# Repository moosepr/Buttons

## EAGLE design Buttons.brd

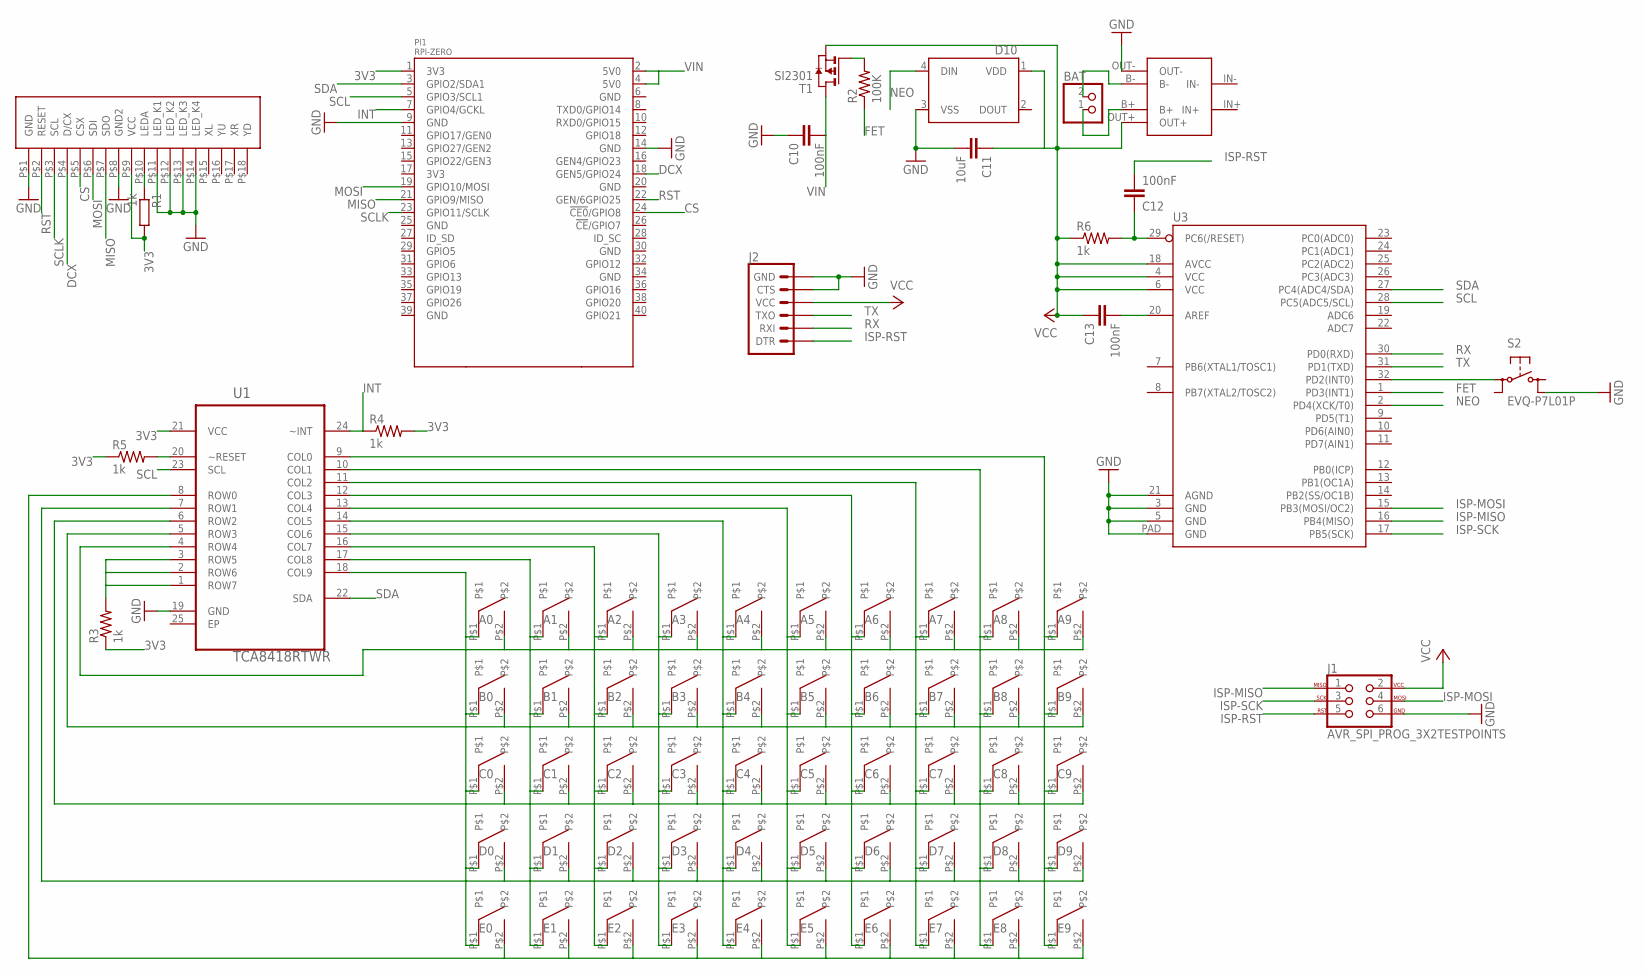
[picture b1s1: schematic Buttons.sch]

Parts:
A0, A1, A2, A3, A4, A5, A6, A7, A8, A9: 5MMSNAP
B0, B1, B2, B3, B4, B5, B6, B7, B8, B9: 5MMSNAP
BAT: JST_2PIN-SMT-RA; JST-PH-2-SMT-RA
C0, C1, C2, C3, C4, C5, C6, C7, C8, C9: 5MMSNAP
C10, C12, C13: 100nF; C0603K
C11: 10uF; C0603K
D0, D1, D2, D3, D4, D5, D6, D7, D8, D9: 5MMSNAP
D10: WS2812B
E0, E1, E2, E3, E4, E5, E6, E7, E8, E9: 5MMSNAP
J1: AVR_SPI_PROG_3X2TESTPOINTS; 2X3_TEST_POINTS
J2: 6_PIN_SERIAL_TARGETSILK; 6_PIN_SERIAL_TARGET_SIDE_W_SILK
PI1: RPI-ZERO; RASPBERRYPI_BASTELSTUBE_V13_RASPI_BOARD_B+_FULL
R1: 1k; R0805
R2: 100K; 0603-RES
R3, R4, R5, R6: 1k; 0805
S2: EVQ-P7L01P
T1: SI2301; SOT-23
U1: TCA8418RTWR; QFN50P400X400X80-25N
U3: ATMEGA328P_MLFMLF32; MLF32-PAD
U$1: 03962A
U$2: ILI9341-2.8

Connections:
3V3: PI1.1 (3V3), R1.2, R3.1, R4.2, R5.1, U1.21 (VCC), U$2.P$9 (VCC)
CS: PI1.24 (!CE0!/GPIO8), U$2.P$5 (CSX)
DCX: PI1.18 (GEN5/GPIO24), U$2.P$4 (D/CX)
FET: R2.1, U3.1 (PD3(INT1))
GND: C10.1, C11.2, D10.3 (VSS), J1.6, J2.P$5 (CTS), J2.P$6 (GND), PI1.9 (GND), PI1.14 (GND), S2.B1 (S1), U1.19 (GND), U3.3 (GND), U3.5 (GND), U3.21 (AGND), U3.PAD (GND), U$1.OUT-, U$2.P$1 (GND), U$2.P$8 (GND2), U$2.P$11 (LED_K1), U$2.P$12 (LED_K2), U$2.P$13 (LED_K3), U$2.P$14 (LED_K4)
INT: PI1.7 (GPIO4/GCKL), R4.1, U1.24 (~INT)
ISP-MISO: J1.1, U3.16 (PB4(MISO))
ISP-MOSI: J1.4, U3.15 (PB3(MOSI/OC2))
ISP-RST: C12.2, J1.5, J2.P$1 (DTR)
ISP-SCK: J1.3, U3.17 (PB5(SCK))
MISO: PI1.21 (GPIO9/MISO), U$2.P$7 (SDO)
MOSI: PI1.19 (GPIO10/MOSI), U$2.P$6 (SDI)
unnamed: S2.A, U3.32 (PD2(INT0))
unnamed: C13.2, U3.20 (AREF)
unnamed: C12.1, R6.2, U3.29 (PC6(/RESET))
unnamed: R1.1, U$2.P$10 (LEDA)
unnamed: R3.2, U1.1 (ROW7), U1.2 (ROW6), U1.3 (ROW5)
unnamed: R2.2, T1.3 (G)
unnamed: R5.2, U1.20 (~RESET)
unnamed: A9.P$1, B9.P$1, C9.P$1, D9.P$1, E9.P$1, U1.9 (COL0)
unnamed: A0.P$2, A1.P$2, A2.P$2, A3.P$2, A4.P$2, A5.P$2, A6.P$2, A7.P$2, A8.P$2, A9.P$2, U1.4 (ROW4)
unnamed: B0.P$2, B1.P$2, B2.P$2, B3.P$2, B4.P$2, B5.P$2, B6.P$2, B7.P$2, B8.P$2, B9.P$2, U1.5 (ROW3)
unnamed: C0.P$2, C1.P$2, C2.P$2, C3.P$2, C4.P$2, C5.P$2, C6.P$2, C7.P$2, C8.P$2, C9.P$2, U1.6 (ROW2)
unnamed: D0.P$2, D1.P$2, D2.P$2, D3.P$2, D4.P$2, D5.P$2, D6.P$2, D7.P$2, D8.P$2, D9.P$2, U1.7 (ROW1)
unnamed: E0.P$2, E1.P$2, E2.P$2, E3.P$2, E4.P$2, E5.P$2, E6.P$2, E7.P$2, E8.P$2, E9.P$2, U1.8 (ROW0)
unnamed: BAT.1 (2), U$1.B+
unnamed: BAT.2 (1), U$1.B-
unnamed: A0.P$1, B0.P$1, C0.P$1, D0.P$1, E0.P$1, U1.18 (COL9)
unnamed: A1.P$1, B1.P$1, C1.P$1, D1.P$1, E1.P$1, U1.17 (COL8)
unnamed: A2.P$1, B2.P$1, C2.P$1, D2.P$1, E2.P$1, U1.16 (COL7)
unnamed: A3.P$1, B3.P$1, C3.P$1, D3.P$1, E3.P$1, U1.15 (COL6)
unnamed: A4.P$1, B4.P$1, C4.P$1, D4.P$1, E4.P$1, U1.14 (COL5)
unnamed: A5.P$1, B5.P$1, C5.P$1, D5.P$1, E5.P$1, U1.13 (COL4)
unnamed: A6.P$1, B6.P$1, C6.P$1, D6.P$1, E6.P$1, U1.12 (COL3)
unnamed: A7.P$1, B7.P$1, C7.P$1, D7.P$1, E7.P$1, U1.11 (COL2)
unnamed: A8.P$1, B8.P$1, C8.P$1, D8.P$1, E8.P$1, U1.10 (COL1)
NEO: D10.4 (DIN), U3.2 (PD4(XCK/T0))
RST: PI1.22 (GEN/6GPIO25), U$2.P$2 (RESET)
RX: J2.P$3 (RXI), U3.30 (PD0(RXD))
SCL: PI1.5 (GPIO3/SCL1), U1.23 (SCL), U3.28 (PC5(ADC5/SCL))
SCLK: PI1.23 (GPIO11/SCLK), U$2.P$3 (SCL)
SDA: PI1.3 (GPIO2/SDA1), U1.22 (SDA), U3.27 (PC4(ADC4/SDA))
TX: J2.P$2 (TXO), U3.31 (PD1(TXD))
VCC: C11.1, C13.1, D10.1 (VDD), J1.2, J2.P$4 (VCC), R6.1, T1.2 (S), U3.4 (VCC), U3.6 (VCC), U3.18 (AVCC), U$1.OUT+
VIN: C10.2, PI1.2 (5V0), PI1.4 (5V0), T1.1 (D)

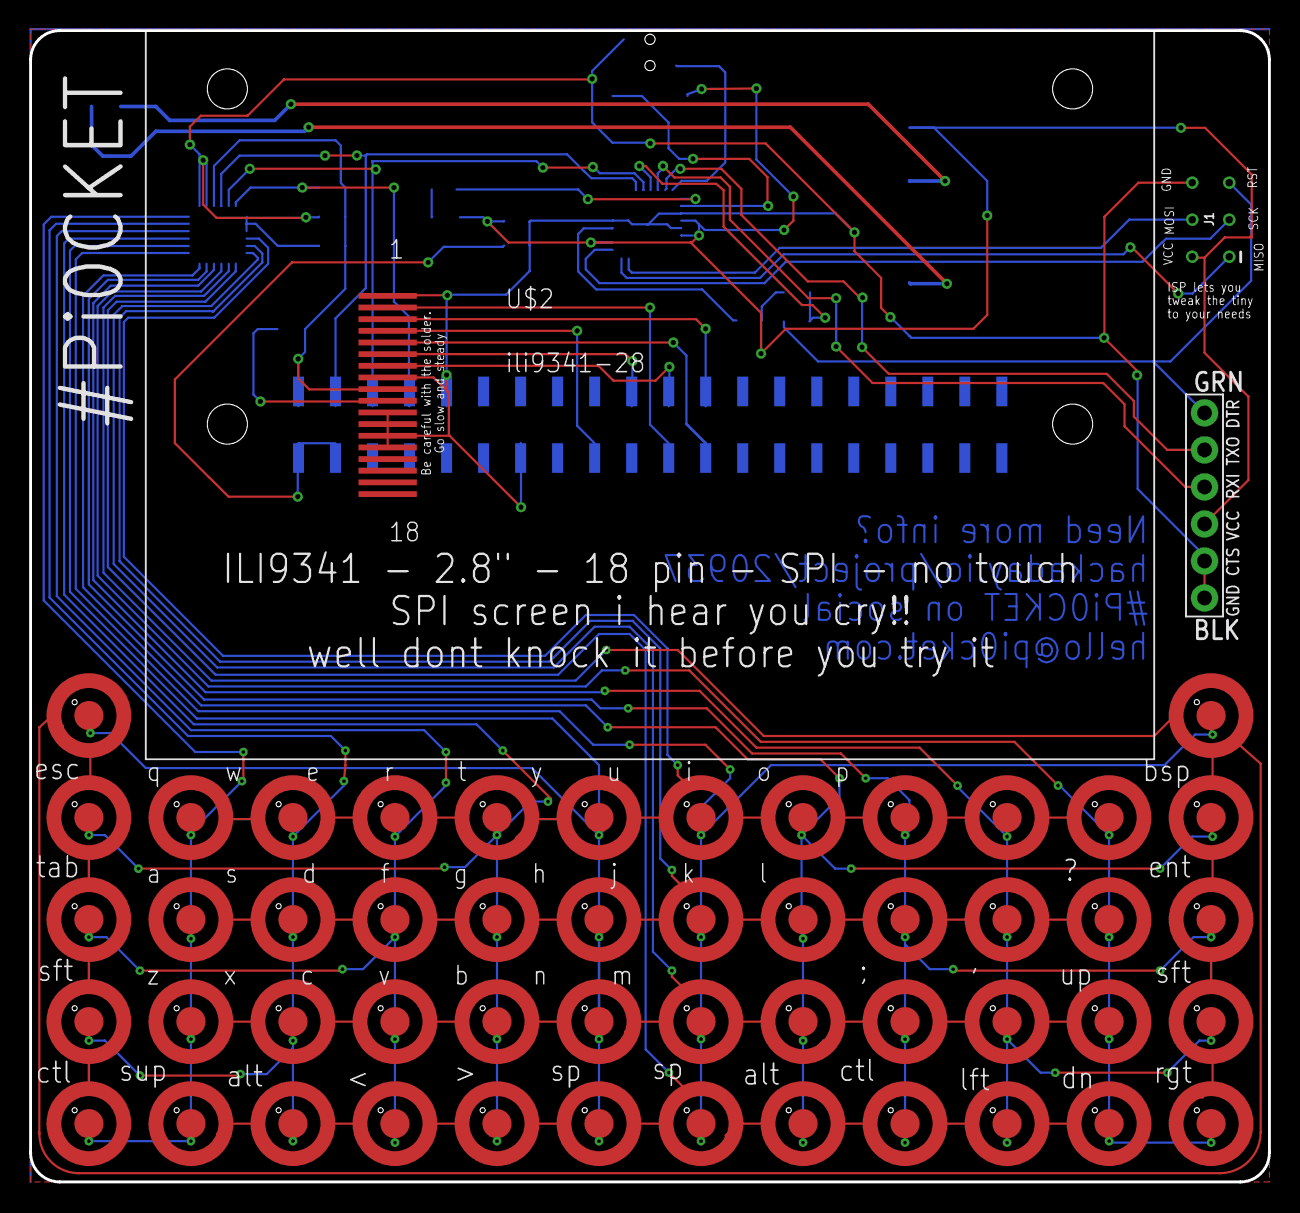
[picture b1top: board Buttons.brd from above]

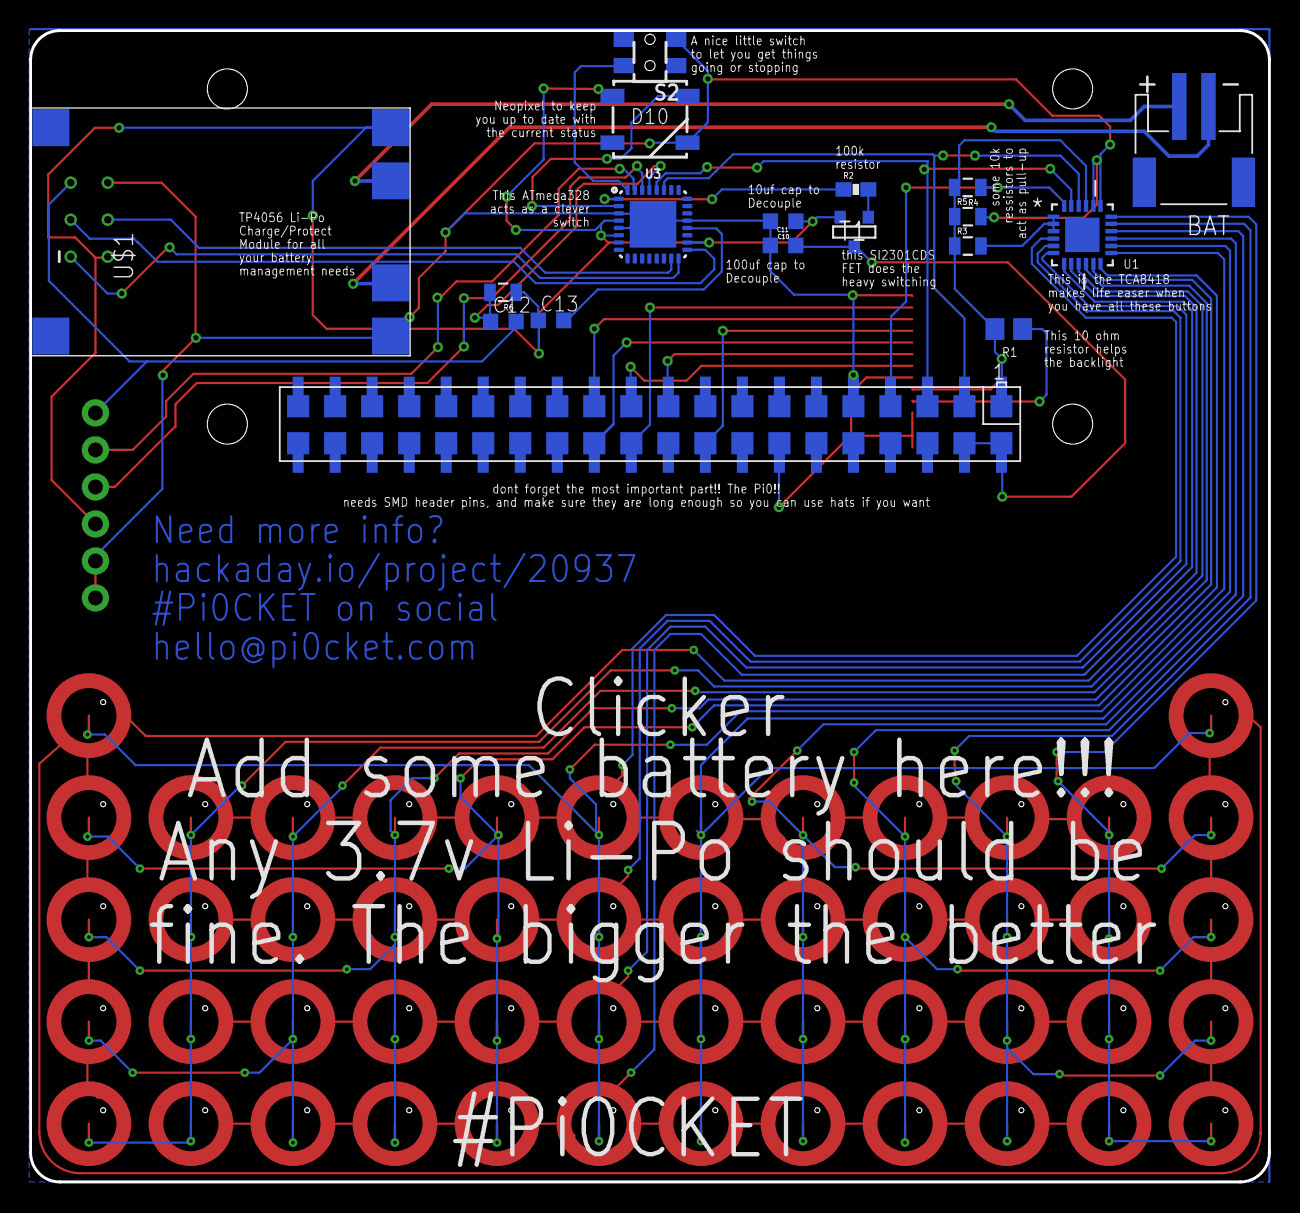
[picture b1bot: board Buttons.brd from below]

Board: 2 copper layers, 85.0 x 79.0 mm, 71 parts (18 on the bottom side), 45 nets.

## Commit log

2017-04-16 in the begining, peter created the pcb, and it was without form and void
2017-08-17 getting there!!
2017-08-22 this could be the one neo!
2017-08-23 nailed it!
2017-08-25 final?
2017-11-05 changed the tiny85 to a tiny88, the power button is now a side press jobby, and moved to the back along with the neopixel.
2017-11-05 some polish
2018-01-16 changed to atmega328
2018-02-27 fixed issue with power button footprint

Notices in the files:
parts and their libraries:
SparkFun-Passives: Licensing: CC v3.0 Share-Alike You are welcome to use this library for commercial purposes.
SparkFun-LED: Licensing: Creative Commons ShareAlike 4.0 International - https://creativecommons.org/licenses/by-sa/4.0
switch-panasonic: Copyright (C) 2010, Bob Starr
